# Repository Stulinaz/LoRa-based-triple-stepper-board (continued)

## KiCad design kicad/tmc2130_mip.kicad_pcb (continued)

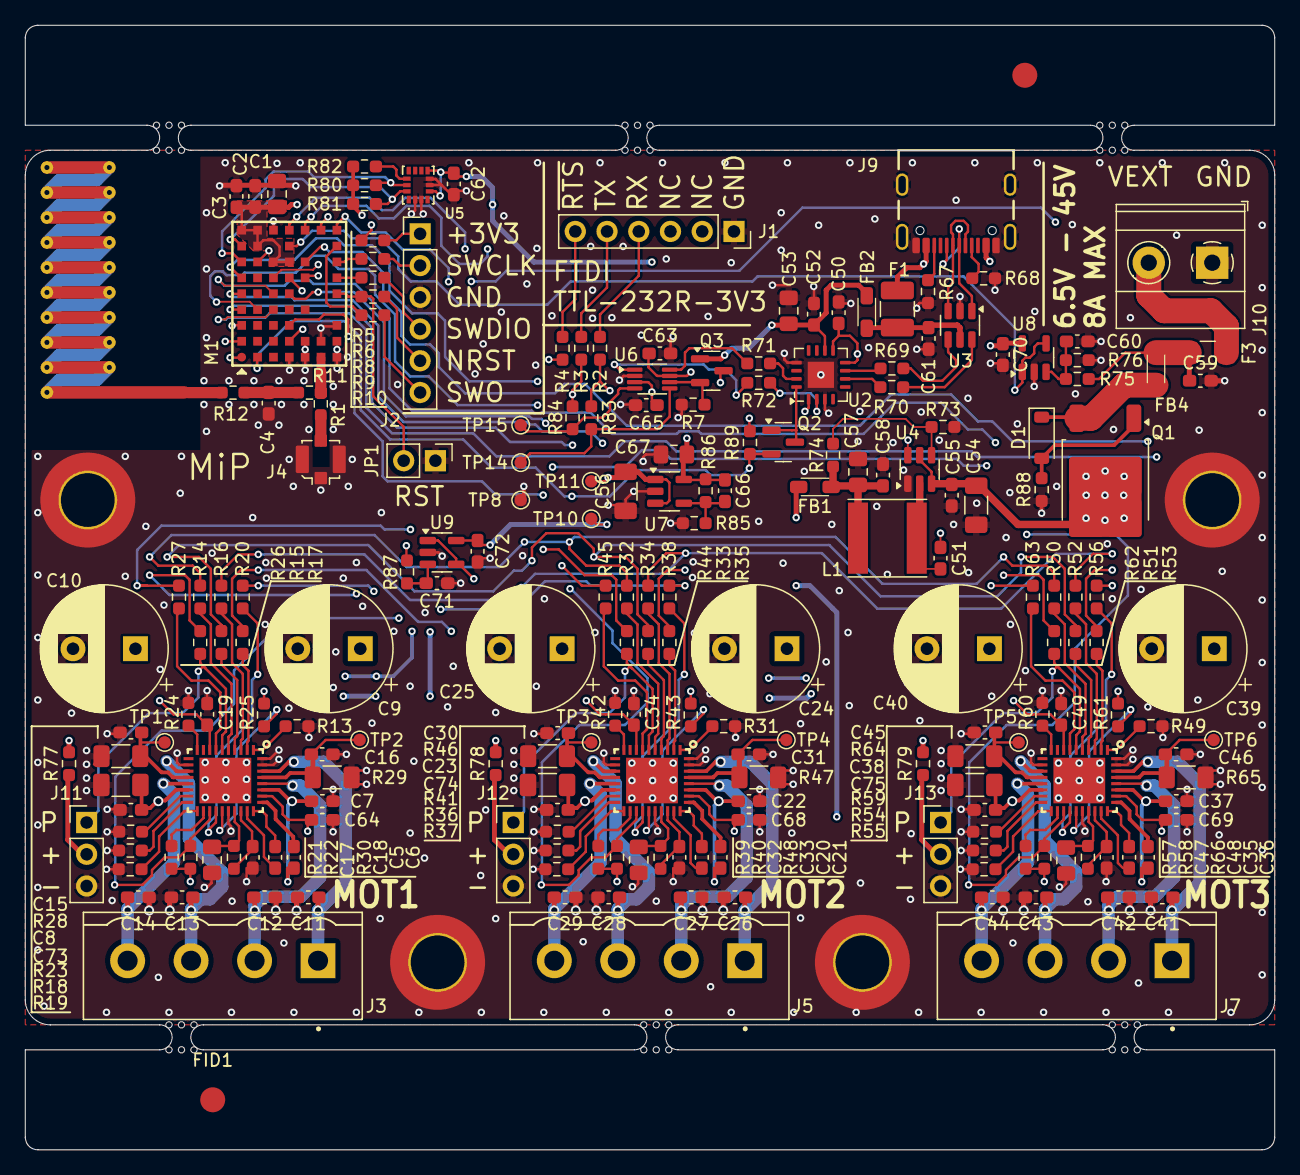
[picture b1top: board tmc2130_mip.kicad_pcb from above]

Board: 4 copper layers, 100.0 x 90.0 mm, 219 parts (0 on the bottom side), 156 nets.

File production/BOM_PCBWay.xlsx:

|  |  | LoRa based triple stepper board PCS BOM
Item # | *Designator | *Qty | Manufacturer | *Mfg Part # | Description / Value | *Package/Footprint | Type | Your Instructions / Notes
1 | C1,C17,C32,C47,C53,C57,C67 | 7 | MURATA | GRM21BR71C475KE51L | Multilayer Ceramic Capacitors MLCC - SMD/SMT 4.7 uF 16 VDC 10% 0805 X7R | C0805 | SMD
2 | C2,C3,C6,C7,C19,C21,C22,C34,C36,C37,C49,C50,C51,C52,C55,C58,C59,C60,C61,C63,C64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 | 30 | SAMSUNG | CL10B104KC8NNNC | Multilayer Ceramic Capacitors MLCC - SMD/SMT 100nF+/-10% 100V X7R 0603 | C0603 | SMD
3 | C5,C20,C35 | 3 | TDK | C1608X7R1H223K080AA | Multilayer Ceramic Capacitors MLCC - SMD/SMT 0603 50VDC 22nF 10% X7R 0.8mm | C0603 | SMD
4 | C8,C23,C38,C54 | 4 | MURATA | GRM31CZ72A475KE11L | Multilayer Ceramic Capacitors MLCC - SMD/SMT 4.7 uF 100 VDC 10% 1206 X7R | C1206 | SMD
5 | C9,C24,C39 | 3 | YAGEO | C0603C221J5GACAUTO7411 | Multilayer Ceramic Capacitors MLCC - SMD/SMT 50V 220pF C0G 0603 5% AEC-Q200 | C0603 | SMD
6 | D1 | 1 | NEXPERIA | BZT52-C13J | Zener Diodes BZT52-C13/SOD123/SOD2 | SOD-123-2 | SMD
7 | F1 | 1 | LITTLEFUSE | MICROSMD050F-2 | Resettable Fuses - PPTC .5A 13.2V 40A Imax | 1210 | SMD
8 | F3 | 1 | BOURNS | SF-1206HH1200R-2 | Surface Mount Fuses 1206 high-current met-foil. 12A | 1206 | SMD
9 | FB1,FB2,FB4 | 3 | WURTH ELEKTRONIK | 742792030 | Ferrite Beads WE-CBF 3mOhms 10K mA805 AEC-Q200 | 0805 | SMD
10 | J3,J5,J7 | 3 | PHOENIX CONTACT | 1755752 | Pluggable Terminal Blocks 4 Pos 5.08mm pitch Through Hole Header | Pitch 5.08mm | THT
11 | J4 | 1 | MOLEX | 73412-0110 | RF Connectors / Coaxial Connectors MCX V PCB JACK SMT 1.25MM MNT HGT |  | SMD
12 | J9 | 1 | GCT | USB4105-GF-A | USB Connectors USB Type C,2.0, Rec,SMT, 0.95mmTH Shell Stakes,G/F,RA,Top Mnt,T&R |  | SMD
13 | J10 | 1 | PHOENIX CONTACT | 1987096 | Fixed Terminal Blocks MKDSN 2,5/ 2-5,08 SZS-SCREW | Pitch 5.08mm | SMD
14 | J15,J16,J17 | 3 | PHOENIX CONTACT | 1792265 | Pluggable Terminal Blocks 4 Pos 5.08mm pitch Plug 24-12 AWG Screw
15 | L1 | 1 | TAIYO YUDEN | NRS6028T470MMGJ | Power Inductors - SMD 963-LSXND6060WHL470M RPLCMT PN 6028 47uH 390mOhms |  | SMD
15 | M1 | 1 | MIPOT | 32001505/6CEU | 32001505/6CEU - DUAL CORE LoRa MODULE | LGA | SMD | https://mipot.com/en/products/mip-series/dual-core/32001506deu/
15 | MOT1,MOT2,MOT3 | 3 | ANALOG DEVICES | TMC2130-LA | Motor/Motion/Ignition Controllers & Drivers Silent stepper motor driver 5 to 46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 |  | SMD
15 | Q1 | 1 | DIODES INCORPORATED | DMPH6050SK3-13 | MOSFETs MOSFET BVDSS | DPAK-3 | SMD
15 | Q2,Q3 | 2 | DIODES INCORPORATED | BS870-7-F | MOSFETs 60V 310mW | SOT-23-3 | SMD
15 | R2,R3,R4,R5,R6,R8,R9,R10,R14,R15,R16,R17,R20,R26,R27,R32,R33,R34,R35,R38,R44,R4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 | 35 | YAGEO | AC0603JR-0722RL | Thick Film Resistors - SMD 22 Ohms 100 mW 0603 5% AEC-Q200 Standard Power Versi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 | R0603 | SMD
15 | R7,R74,R88 | 3 | YAGEO | RT0603FRE07360KL | Thick Film Resistors - SMD 360k Ohms 100 mW 0603 5% AEC-Q200 Standard Power Ver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 | R0603 | SMD
15 | R11,R12,R13,R18,R19,R23,R25,R31,R36,R37,R41,R43,R49,R54,R55,R59,R61 | 17 | YAGEO | RC0603FR-100RL | Thick Film Resistors - SMD 0 Ohms 100-200mW 0603 1% | R0603 | SMD
15 | R21,R22,R39,R40,R57,R58,R87,R89 | 8 | YAGEO | RC0603JR-0710KL | Thick Film Resistors - SMD 10 kOhms 100 mW 0603 5% | R0603 | SMD
15 | R28,R29,R46,R47,R64,R65 | 6 | YAGEO | RL1206FR-070R22L | Current Sense Resistors - SMD 220 mOhms 250mW 1 % 600 ppm/C | R1206 | SMD
15 | R30,R48,R66 | 3 | YAGEO | RC0603JR-072R2L | Thick Film Resistors - SMD 2.2 Ohms 100 mW 0603 5% | R0603 | SMD
15 | R67,R68 | 2 | YAGEO | RC0603FR-105K1L | Thick Film Resistors - SMD 5.1kOhms 1/10W 0603 1% | R0603 | SMD
15 | R73,R76 | 2 | YAGEO | RC0402FR-0756K2L | Thick Film Resistors - SMD 56.2 kOhms 62.5mW 0402 1% | R0402 | SMD
15 | R75 | 1 | YAGEO | RC0603FR-071ML | Thick Film Resistors - SMD 1 MOhms 100mW 0603 1% | R0603 | SMD
15 | R75 | 1 | YAGEO | RC0402FR-0718KL | Thick Film Resistors - SMD 18 kOhms 62.5mW 0402 1% | R0402 | SMD
15 | R86 | 1 | YAGEO | RC0402FR-0756K2L | Thick Film Resistors - SMD 56.2 kOhms 62.5mW 0402 1% | R0603 | SMD
15 | U2 | 1 | FTDI | FT230XQ-R | USB Interface IC USB to Basic Serial UART IC QFN-16 | QFN16 | SMD
15 | U3 | 1 | STMICROELECTRONICS | USBLC6-2SC6 | ESD Protection Diodes / TVS Diodes ESD Protection Low Cap | SOT23-6 | SMD
15 | U4 | 1 | TEXAS INSTRUMENTS | LMR51610XDBVR | Switching Voltage Regulators SIMPLE SWITCHER power converter with 4.5V-to-65V 1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 | SOT23-6 | SMD
15 | U6 | 1 | TEXAS INSTRUMENTS | TXS0102DCUR | Translation - Voltage Levels 2-Bit Bi-Directional Voltage-Level-Trans | VSSOP-8 | SMD
15 | U7 | 1 | DIODES INCORPORATED | AP2127K-ADJTRG1 | LDO Voltage Regulators 300mA CMOS LDO 2.5V to 6V | SOT23-5 | SMD
15 | U8,U9 | 2 | MICROCHIP | MCP6001T-E/OT | Operational Amplifiers - Op Amps Single 1.8V 1MHz | SOT23-5 | SMD

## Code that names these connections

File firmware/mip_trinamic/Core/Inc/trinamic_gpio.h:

#ifndef CORE_INC_TRINAMIC_GPIO_H_
#define CORE_INC_TRINAMIC_GPIO_H_

/*******************************************************************************
 * Included files
 *****************************************************************************/
#include "main.h"

/*******************************************************************************
 * Definitions
 ******************************************************************************/

#define TRINAMIC_MOT0_ID 0
#define TRINAMIC_MOT1_ID 1
#define TRINAMIC_MOT2_ID 2

/* MOT 0 */
#define DRV0_STEP_Pin			GPIO_PIN_10
#define DRV0_STEP_Port 			GPIOB

#define DRV0_DIR_Pin			GPIO_PIN_6
#define DRV0_DIR_Port  			GPIOA

#define DRV0_EN_Pin				GPIO_PIN_5
#define DRV0_EN_Port  			GPIOA

#define DRV0_DIAGNOSTIC_Pin		GPIO_PIN_2
#define DRV0_DIAGNOSTIC_Port  	GPIOB

#define DRV0_SPI_NSS_Pin		GPIO_PIN_4
#define DRV0_SPI_NSS_Port  		GPIOA

/* MOT 1 */
#define DRV1_STEP_Pin			GPIO_PIN_11
#define DRV1_STEP_Port 			GPIOB

#define DRV1_DIR_Pin			GPIO_PIN_14
#define DRV1_DIR_Port  			GPIOB

#define DRV1_EN_Pin		        GPIO_PIN_4
#define DRV1_EN_Port	        GPIOB

#define DRV1_DIAGNOSTIC_Pin		GPIO_PIN_3
#define DRV1_DIAGNOSTIC_Port	GPIOA

#define DRV1_SPI_NSS_Pin		GPIO_PIN_12
#define DRV1_SPI_NSS_Port  		GPIOB

/* MOT 2 */
#define DRV2_EN_Pin		        GPIO_PIN_1
#define DRV2_EN_Port	        GPIOA

#define DRV2_STEP_Pin		    GPIO_PIN_0
#define DRV2_STEP_Port	        GPIOA

#define DRV2_DIR_Pin			GPIO_PIN_5
#define DRV2_DIR_Port 			GPIOB

#define DRV2_DIAGNOSTIC_Pin		GPIO_PIN_15
#define DRV2_DIAGNOSTIC_Port	GPIOA

#define DRV2_SPI_NSS_Pin		GPIO_PIN_12
#define DRV2_SPI_NSS_Port  		GPIOA

/* SPI */
#define SPI2_MOSI_Pin			GPIO_PIN_3
#define SPI2_MOSI_Port  		GPIOC

#define SPI2_MISO_Pin			GPIO_PIN_2
#define SPI2_MISO_Port  		GPIOC

#define SPI2_CLK_Pin			GPIO_PIN_9
#define SPI2_CLK_Port  		    GPIOA

/* FTDI */
#define MOD_TX_Pin				GPIO_PIN_0
#define MOD_TX_Port				GPIOC

#define MOD_RX_Pin				GPIO_PIN_1
#define MOD_RX_Port				GPIOC

#define MOD_NWAKE_Pin			GPIO_PIN_7
#define MOD_NWAKE_Port			GPIOA

/* IIC */
#define IIC_SCL_Pin				GPIO_PIN_8
#define IIC_SCL_Port			GPIOB

#define IIC_SDA_Pin				GPIO_PIN_9
#define IIC_SDA_Port			GPIOB

/* GPIO DEBUG */
#define GPIO0_NWAKE_Pin			GPIO_PIN_7
#define GPIO0_NWAKE_Port		GPIOA

/* BATTERY MEASUREMENT & DAC */
#define AIN_REF_MIP_Pin			GPIO_PIN_10
#define AIN_REF_MIP_Port  		GPIOA

#define VEXT_SENSE_Pin			GPIO_PIN_13
#define VEXT_SENSE_Port  		GPIOB

/*******************************************************************************
* API
******************************************************************************/
void TrinamicGPIO_Init(void);
void TrinamicNSS_Select(uint8_t driver);
void TrinamicNSS_Idle(void);
void TrinamicMotXEnable(uint8_t driver);
void TrinamicMotXDisable(uint8_t driver);

#endif

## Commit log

2025-01-07 added pcbway format bom, added pcb production document
2025-01-07 added LICENSE.md
2025-01-08 added sch images
2025-01-08 added firmware schematic implementation img
2025-01-10 fixed bom, cortex m0 wakeup ok
2025-01-10 added LoRa module Driver, Module demo app running
2025-01-10 remodev unnecessary files
2025-01-17 fixed layout error on u4
2025-01-17 removed stencil files, updated README
2025-01-17 spi ok, all 3 drivers completed init procedure, first steps with stepper
2025-01-17 added new images, linked to PCBWay
2025-01-17 added more developing img
2025-01-17 added closeup images and warning
2025-01-21 added dac for drive tmc ai_iref pins
2025-02-06 output 2.5 from dac pin to trinamic drivers
2025-02-07 board transmits correctly radio frames
